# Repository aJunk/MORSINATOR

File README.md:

# Morsinator

This repository contains the design files and code for the MORSINATOR.
The MORSINATOR is a morse code transceiver developed for application in scout group activities.

## Overview
The MORSINATOR is an RS485-based Hardware interface for transmitting morse code over several hundred meters across twin telecom/telephone wiring.

It does not transmit data, just high and low pulses.

## Future development

The board contains space and components for integrating an ESP32C3 microcontroller. It can Intercept the user input and line output.
It can be used to automate message sending and receiving, coordinate between stations, and more.

Code for it is not finished yet and will be added once in a presentable state.

## License
This project is licensed under the GPLv3.

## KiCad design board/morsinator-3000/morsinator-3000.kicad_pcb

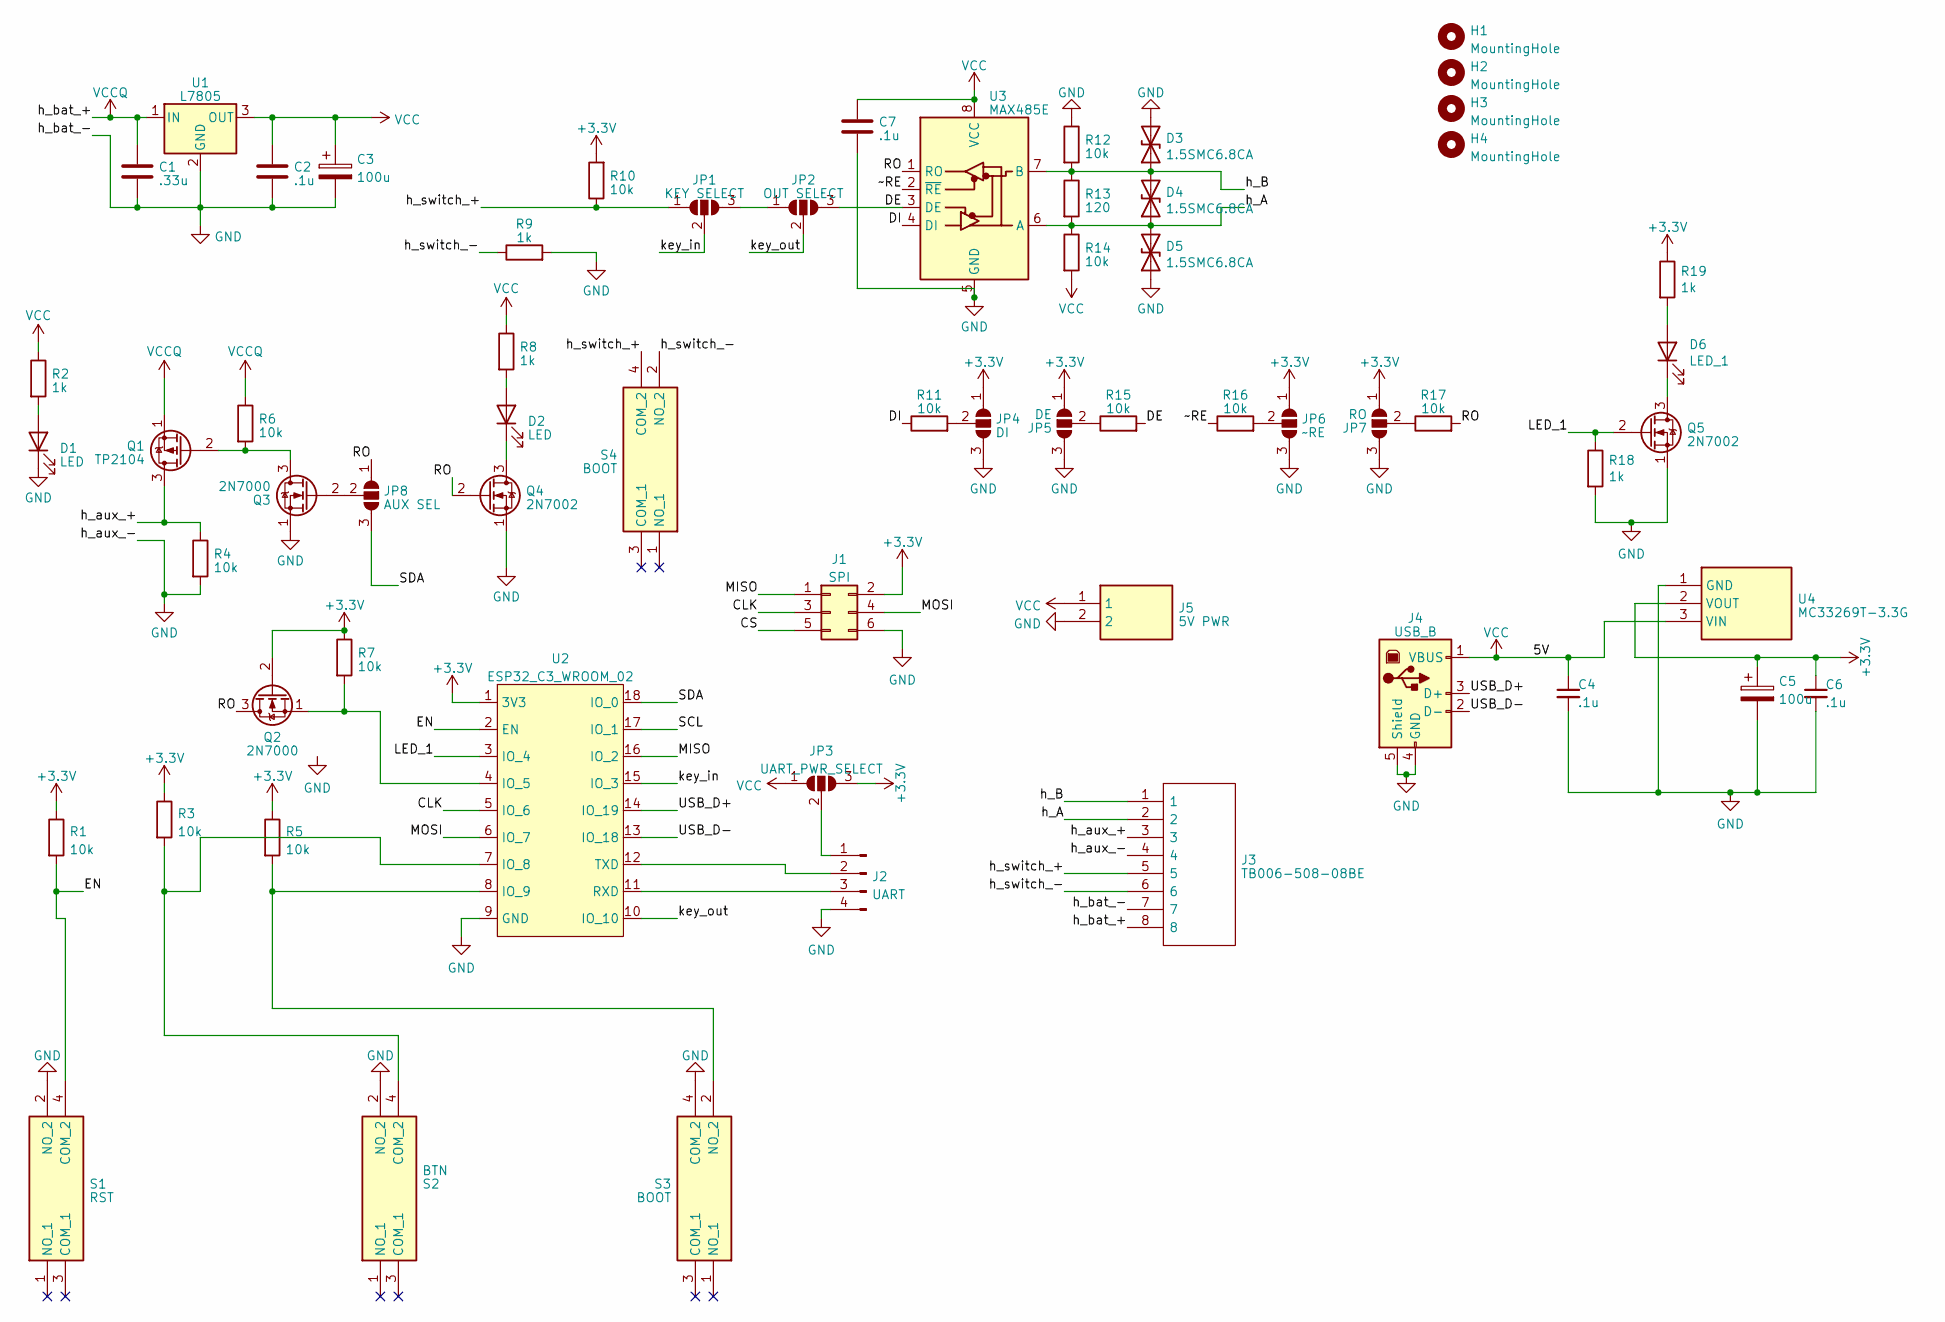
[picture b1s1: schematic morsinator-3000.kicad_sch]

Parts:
C1: .33u; C_Rect_L7.0mm_W2.5mm_P5.00mm
C2, C4, C6, C7: .1u; C_Rect_L7.0mm_W2.5mm_P5.00mm
C3, C5: 100u; CP_Radial_D4.0mm_P2.00mm
D1, D2: LED; LED_D5.0mm
D3, D4, D5: 1.5SMC6.8CA; D_DO-15_P10.16mm_Horizontal
D6: LED_1; LED_D5.0mm
H1, H2, H3, H4: MountingHole; MountingHole_3.2mm_M3_DIN965_Pad_TopBottom
J1: SPI; PinHeader_2x03_P2.54mm_Vertical
J2: UART; PinHeader_1x04_P2.54mm_Vertical
J3: TB006-508-08BE; TB00650808BE; Mouser Part Number 490-TB006-508-08BE
J4: USB_B; USB_B_OST_USB-B1HSxx_Horizontal
J5: 5V PWR; SHDR2W100P0X508_1X2_1016X1020X1410P; Mouser Part Number 490-TB004-508-02BE
JP1: KEY SELECT; SolderJumper-3_P1.3mm_Open_RoundedPad1.0x1.5mm_NumberLabels
JP2: OUT SELECT; SolderJumper-3_P1.3mm_Open_RoundedPad1.0x1.5mm_NumberLabels
JP3: UART_PWR_SELECT; SolderJumper-3_P1.3mm_Open_RoundedPad1.0x1.5mm_NumberLabels
JP4: DI; SolderJumper-3_P1.3mm_Open_RoundedPad1.0x1.5mm_NumberLabels
JP5: DE; SolderJumper-3_P1.3mm_Open_RoundedPad1.0x1.5mm_NumberLabels
JP6: ~RE; SolderJumper-3_P1.3mm_Open_RoundedPad1.0x1.5mm_NumberLabels
JP7: RO; SolderJumper-3_P1.3mm_Open_RoundedPad1.0x1.5mm_NumberLabels
JP8: AUX SEL; SolderJumper-3_P1.3mm_Open_RoundedPad1.0x1.5mm_NumberLabels
Q1: TP2104; TO-92_Inline_Wide
Q2, Q3: 2N7000; TO-92_Inline_Wide
Q4, Q5: 2N7002; TO-92_Inline_Wide
R1, R3, R4, R5, R6, R7, R10, R11, R12, R14, R15, R16, R17: 10k; R_Axial_DIN0207_L6.3mm_D2.5mm_P7.62mm_Horizontal
R2, R8, R9, R18, R19: 1k; R_Axial_DIN0207_L6.3mm_D2.5mm_P7.62mm_Horizontal
R13: 120; R_Axial_DIN0207_L6.3mm_D2.5mm_P7.62mm_Horizontal
S1: RST; TS026643BK100SCRD; Mouser Part Number 179-TS026643BK100SCR
S2: BTN; TS026643BK100SCRD; Mouser Part Number 179-TS026643BK100SCR
S3, S4: BOOT; TS026643BK100SCRD; Mouser Part Number 179-TS026643BK100SCR
U1: L7805; TO-220-3_Horizontal_TabDown
U2: ESP32_C3_WROOM_02; ESP32C3WROOM02N4
U3: MAX485E; DIP-8_W7.62mm_Socket
U4: MC33269T-3.3G; TO-220-3_Horizontal_TabDown; Mouser Part Number 863-MC33269T-3.3G

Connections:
+3V3: C5.1, C6.1, J1.2, JP3.3 (B), JP4.1 (A), JP5.1 (A), JP6.1 (A), JP7.1 (A), Q2.2 (G), R1.1, R3.1, R5.1, R7.1, R10.2, R19.1, U2.1 (3V3), U4.2 (VOUT)
/CLK: J1.3, U2.5 (IO_6)
/CS: J1.5
/DE: JP2.3 (B), R15.2, U3.3 (DE)
/DI: R11.1, U3.4 (DI)
/EN: R1.2, S1.4 (COM_2), U2.2 (EN)
/LED_1: Q5.2 (G), R18.1, U2.3 (IO_4)
/MISO: J1.1, U2.16 (IO_2)
/MOSI: J1.4, U2.6 (IO_7)
/RO: JP8.1 (A), Q2.3 (D), Q4.2 (G), R17.2, U3.1 (RO)
/SCL: U2.17 (IO_1)
/SDA: JP8.3 (B), U2.18 (IO_0)
/USB_D+: J4.3 (D+), U2.14 (IO_19)
/USB_D-: J4.2 (D-), U2.13 (IO_18)
/h_A: D4.1 (A1), D5.2 (A2), J3.2, R13.2, R14.1, U3.6 (A)
/h_B: D3.1 (A1), D4.2 (A2), J3.1, R12.2, R13.1, U3.7 (B)
/h_aux_+: J3.3, Q1.3 (D), R4.1
/h_switch_+: J3.5, JP1.1 (A), R10.1, S4.4 (COM_2)
/h_switch_-: J3.6, R9.1, S4.2 (NO_2)
/key_in: JP1.2 (C), U2.15 (IO_3)
/key_out: JP2.2 (C), U2.10 (IO_10)
/~RE: R16.1, U3.2 (~RE)
GND: C1.2, C2.2, C3.2, C4.2, C5.2, C6.2, C7.2, D1.1 (K), D3.2 (A2), D5.1 (A1), J1.6, J2.4, J3.4, J3.7, J4.4 (GND), J4.5 (Shield), J5.2, JP4.3 (B), JP5.3 (B), JP6.3 (B), JP7.3 (B), Q3.1 (S), Q4.1 (S), Q5.1 (S), R4.2, R9.2, R12.1, R18.2, S1.2 (NO_2), S2.2 (NO_2), S3.4 (COM_2), U1.2 (GND), U2.9 (GND), U3.5 (GND), U4.1 (GND)
unnamed: D1.2 (A), R2.2
unnamed: D2.2 (A), R8.2
unnamed: D2.1 (K), Q4.3 (D)
unnamed: D6.2 (A), R19.2
unnamed: D6.1 (K), Q5.3 (D)
unnamed: J2.1, JP3.2 (C)
unnamed: J2.2, U2.12 (TXD)
unnamed: J2.3, U2.11 (RXD)
unnamed: JP1.3 (B), JP2.1 (A)
unnamed: JP4.2 (C), R11.2
unnamed: JP5.2 (C), R15.1
unnamed: JP6.2 (C), R16.2
unnamed: JP7.2 (C), R17.1
unnamed: JP8.2 (C), Q3.2 (G)
unnamed: Q1.2 (G), Q3.3 (D), R6.2
unnamed: Q2.1 (S), R7.2, U2.4 (IO_5)
unnamed: R3.2, S2.4 (COM_2), U2.7 (IO_8)
unnamed: R5.2, S3.2 (NO_2), U2.8 (IO_9)
VCC: C2.1, C3.1, C4.1, C7.1, J4.1 (VBUS), J5.1, JP3.1 (A), R2.1, R8.1, R14.2, U1.3 (OUT), U3.8 (VCC), U4.3 (VIN)
VCCQ: C1.1, J3.8, Q1.1 (S), R6.1, U1.1 (IN)

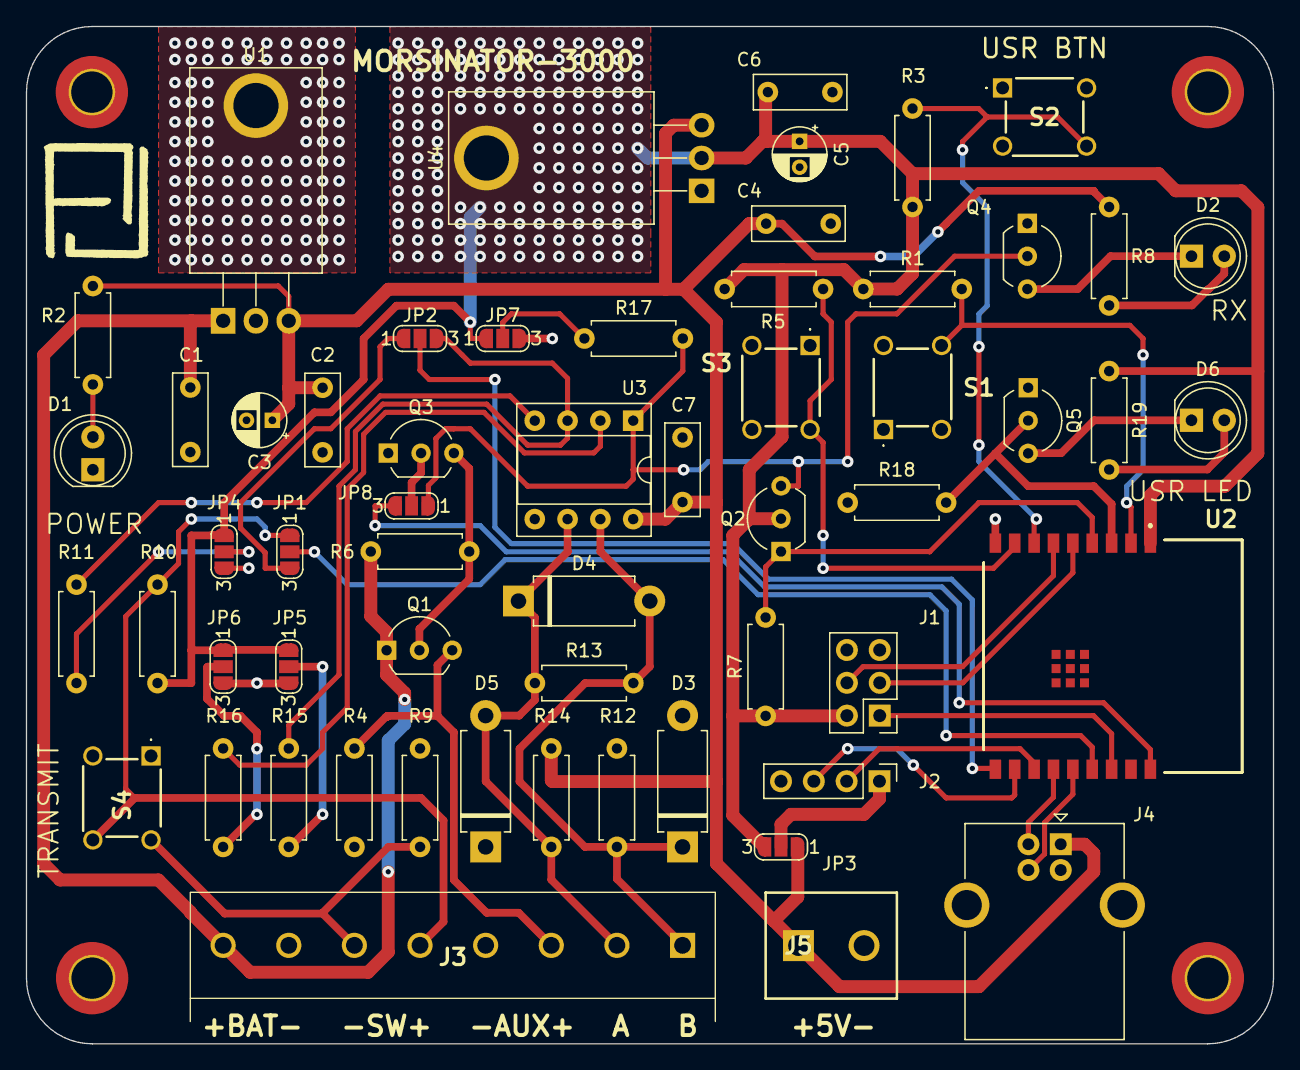
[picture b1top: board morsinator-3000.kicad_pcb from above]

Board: 2 copper layers, 96.5 x 78.7 mm, 62 parts (0 on the bottom side), 41 nets.
